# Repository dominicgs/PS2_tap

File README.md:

PS/2 Tap
========

A PS/2 data tap over audio line in.

Why?
----
I thought it would be a fun thing to do.

How?
----
PS/2 keyboards transmit data at between 11 and 16 kHz, which is easily within
range of every modern sound card.  This board and software allow a user to tap
a PS/2 line and read the transmitted keyboard data via the line in socket on the
host.

The data could also be transmitted over a radio link, although loss in quality
would hamper decoding of the data.

BOM
---
- 2x PS/2 connectors (mini-din 6): On Shore Technology Inc, MD-6006 connectors - http://www.digikey.com/product-search/en/connectors-interconnects/circular-connectors/1443097?k=md%206006
- 2x 3.5mm Jack: Switchcraft Inc, 35RASMT2BHNTRX -  http://www.digikey.com/product-detail/en/35RASMT2BHNTRX/SC1489-1-ND/2754494
- 2x 2k2 resistor:  - 
- 2x 1k resistor:  -

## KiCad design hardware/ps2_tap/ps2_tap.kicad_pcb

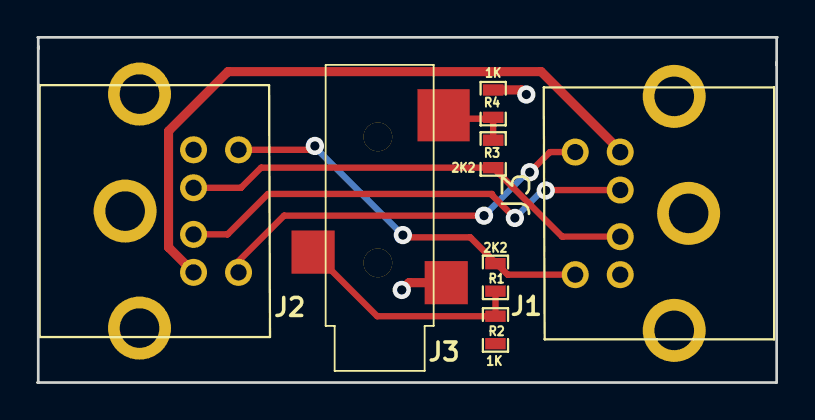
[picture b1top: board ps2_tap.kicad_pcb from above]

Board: 2 copper layers, 41.1 x 19.2 mm, 7 parts (0 on the bottom side), 8 nets.

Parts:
J1, J2: MINI_DIN_6; MD-6006
J3: JACK_NO_SWITCH; JACK_35MM_NO_SWITCH
R1, R3: 2K2; SM0603_Resistor
R2, R4: 1K; SM0603_Resistor

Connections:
/CLK: J1.5, J2.5, R1.1
/CLK_OUT: J3.3, R1.2, R2.1
/DATA: J1.1, J2.1, R3.1
/DATA_OUT: J3.2, R3.2, R4.1
/M_CLK: J1.6, J2.6
/M_DATA: J1.2, J2.2
/VCC: J1.4, J2.4
GND: J1.3, J2.3, J3.1, R2.2, R4.2

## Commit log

2013-05-16 Initial commit of PS/2 data tap designs
2013-05-16 Fix broken list in readme
2013-06-12 Fix swapped 3.5mm jack pads
